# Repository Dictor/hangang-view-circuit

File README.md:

# hangang-view circuit
This is schemetic and gerber files repository of hangang-view project. Main code (MCU's firmware) is in [here](https://github.com/Dictor/hangang-view-code).

## schemetic image

## mcu pinout

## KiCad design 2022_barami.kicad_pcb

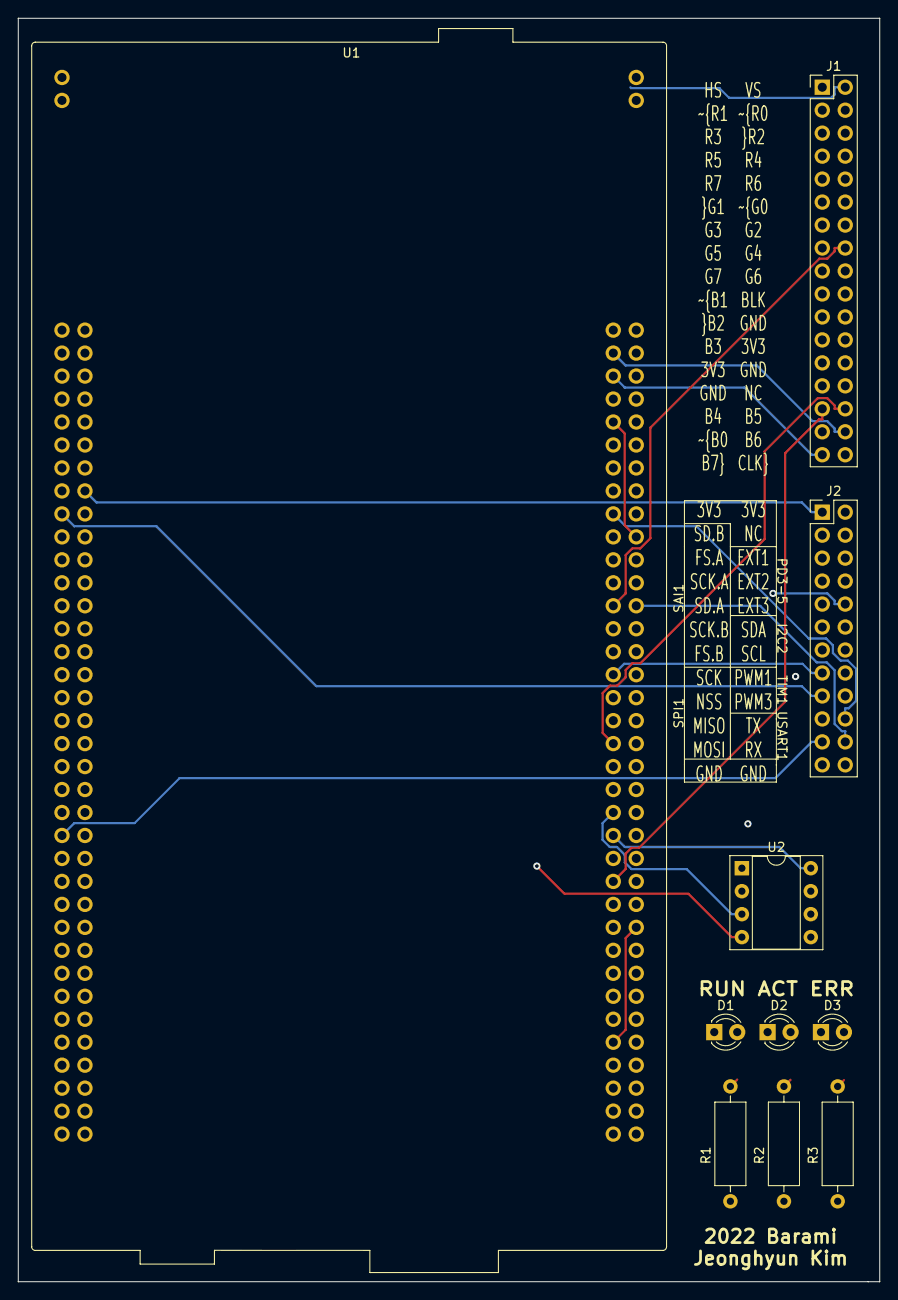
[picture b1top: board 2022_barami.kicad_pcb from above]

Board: 4 copper layers, 95.2 x 139.7 mm, 10 parts (0 on the bottom side), 53 nets.

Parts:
D1: LED_RUN; LED_D3.0mm
D2: LED_ACT; LED_D3.0mm
D3: LED_ERR; LED_D3.0mm
J1: GM7123 Module; PinHeader_2x17_P2.54mm_Vertical
J2: External IO; PinHeader_2x12_P2.54mm_Vertical
R1, R2, R3: 100R; R_Axial_DIN0309_L9.0mm_D3.2mm_P12.70mm_Horizontal
U1: NUCLEO144-H743ZI; ST_Morpho_Connector_144_STLink
U2: 23LC1024-E/P; DIP-8_W7.62mm_Socket

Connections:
+3V3: J1.24, J1.25, J2.1, J2.2, U1.16, U2.2
GND: D1.1, D2.1, D3.1, J1.3, J1.4, J1.6, J1.11, J1.12, J1.19, J1.21, J1.22, J1.26, J1.27, J1.31, J2.23, J2.24, U1.8, U1.19, U1.20, U1.22, U1.49, U1.60, U1.71, U1.72, U1.81, U1.92, U1.104, U1.111, U1.126, U1.135, U1.143, U1.144, U2.7
GPIO_EXT1: J2.6, U1.40
GPIO_EXT2: J2.8, U1.39
GPIO_EXT3: J2.10, U1.41
I2C2_SCL: J2.14, U1.51
I2C2_SDA: J2.12, U1.53
LCD_B3: J1.23, U1.95, U1.137
LCD_B4: J1.29, U1.121
LCD_B5: J1.30, U1.109
LCD_B6: J1.32, U1.75
LCD_B7: J1.33, U1.77
LCD_BLK: J1.20, U1.13
LCD_CLK: J1.34, U1.123
LCD_G2: J1.14, U1.85
LCD_G3: J1.13, U1.128
LCD_G4: J1.16, U1.97
LCD_G5: J1.15, U1.90
LCD_G6: J1.18, U1.91
LCD_G7: J1.17, U1.138
LCD_HSYNC: J1.1, U1.76
LCD_R3: J1.5, U1.34
LCD_R4: J1.8, U1.83
LCD_R5: J1.7, U1.38
LCD_R6: J1.10, U1.96
LCD_R7: J1.9, U1.125
LCD_VSYNC: J1.2, U1.32
LED_ACT: R3.1, U1.4
LED_ERR: R1.1, U1.57
LED_RUN: R2.1, U1.55
unnamed: D1.2, R1.2
unnamed: D2.2, R2.2
unnamed: D3.2, R3.2
QUADSPI_BK1_IO0: U1.117, U2.8
QUADSPI_BK1_IO1: U1.115, U2.3
QUADSPI_BK1_IO2: U1.46, U2.5
QUADSPI_BK1_IO3: U1.9, U2.4
QUADSPI_BK1_NCS: U1.142, U2.1
QUADSPI_CLK: U1.94, U2.6
SAI1_FS_A: J2.5, U1.48
SAI1_FS_B: J2.13, U1.56
SAI1_SCK_A: J2.7, U1.50
SAI1_SCK_B: J2.11, U1.54
SAI1_SD_A: J2.9, U1.62
SAI1_SD_B: J2.3, U1.47
SPI1_MISO: J2.19, U1.63
SPI1_MOSI: J2.21, U1.45
SPI1_NSS: J2.17, U1.17
SPI1_SCK: J2.15, U1.103
TIM1_CH1: J2.16, U1.124
TIM1_CH3: J2.18, U1.127
USART1_RX: J2.22, U1.98
USART1_TX: J2.20, U1.89

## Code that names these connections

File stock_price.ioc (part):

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Mcu.Name=STM32H743ZITx
Mcu.Package=LQFP144
Mcu.UserName=STM32H743ZITx
PA1.Mode=RMII
PA1.Signal=ETH_REF_CLK
PA10.Mode=OTG/Dual_Role_Device
PA10.Signal=USB_OTG_FS_ID
PA11.Mode=OTG/Dual_Role_Device
PA11.Signal=USB_OTG_FS_DM
PA12.Mode=OTG/Dual_Role_Device
PA12.Signal=USB_OTG_FS_DP
PA15\ (JTDI).Mode=NSS_Signal_Hard_Output
PA15\ (JTDI).Signal=SPI1_NSS
PA2.Mode=RMII
PA2.Signal=ETH_MDIO
PA3.Mode=RGB565
PA3.Signal=LTDC_B5
PA4.Mode=RGB565
PA4.Signal=LTDC_VSYNC
PA5.Mode=RGB565
PA5.Signal=LTDC_R4
PA6.Mode=RGB565
PA6.Signal=LTDC_G2
PA7.Mode=RMII
PA7.Signal=ETH_CRS_DV
PA9.Mode=Activate_VBUS
PA9.Signal=USB_OTG_FS_VBUS
PB0.Mode=RGB565
PB0.Signal=LTDC_R3
PB1.Mode=RGB565
PB1.Signal=LTDC_R6
PB10.Mode=RGB565
PB10.Signal=LTDC_G4
PB11.Mode=RGB565
PB11.Signal=LTDC_G5
PB12.Mode=RMII
PB12.Signal=ETH_TXD0
PB13.Mode=RMII
PB13.Signal=ETH_TXD1
PB14.GPIOParameters=GPIO_Label
PB14.GPIO_Label=LD3 [Red Led]
PB14.Signal=GPIO_Output
PB15.Mode=Asynchronous
PB15.Signal=USART1_RX
PB2.Mode=Single Bank 1
PB2.Signal=QUADSPI_CLK
PB3\ (JTDO/TRACESWO).Mode=Full_Duplex_Master
PB3\ (JTDO/TRACESWO).Signal=SPI1_SCK
PB6.Mode=Asynchronous
PB6.Signal=USART1_TX
PB8.Mode=RGB565
PB8.Signal=LTDC_B6
PB9.Mode=RGB565
PB9.Signal=LTDC_B7
PC0.Mode=RGB565
PC0.Signal=LTDC_R5
PC1.Mode=RMII
PC1.Signal=ETH_MDC
PC13.GPIOParameters=GPIO_Label
PC13.GPIO_Label=B1 [Blue PushButton]
PC13.Signal=GPIO_Input
PC14-OSC32_IN\ (OSC32_IN).Mode=LSE-External-Oscillator
PC14-OSC32_IN\ (OSC32_IN).Signal=RCC_OSC32_IN
PC15-OSC32_OUT\ (OSC32_OUT).Mode=LSE-External-Oscillator
PC15-OSC32_OUT\ (OSC32_OUT).Signal=RCC_OSC32_OUT
PC4.Mode=RMII
PC4.Signal=ETH_RXD0
PC5.Mode=RMII
PC5.Signal=ETH_RXD1
PC6.Mode=RGB565
PC6.Signal=LTDC_HSYNC
PC7.Mode=RGB565
PC7.Signal=LTDC_G6
PD0.GPIOParameters=GPIO_Label
PD0.GPIO_Label=LED_ERR
PD0.Signal=GPIO_Output
PD1.GPIOParameters=GPIO_Label
PD1.GPIO_Label=LED_RUN
PD1.Signal=GPIO_Output
PD10.Mode=RGB565
PD10.Signal=LTDC_B3
PD11.Mode=Single Bank 1
PD11.Signal=QUADSPI_BK1_IO0
PD12.Mode=Single Bank 1
PD12.Signal=QUADSPI_BK1_IO1
PD2.GPIOParameters=GPIO_Label
PD2.GPIO_Label=LED_ACT
PD2.Signal=GPIO_Output
PD3.GPIOParameters=GPIO_Label
PD3.GPIO_Label=GPIO_EXT1
PD3.Signal=GPIO_Output
PD4.GPIOParameters=GPIO_Label
PD4.GPIO_Label=GPIO_EXT2
PD4.Signal=GPIO_Output
PD5.GPIOParameters=GPIO_Label
PD5.GPIO_Label=GPIO_EXT3
PD5.Signal=GPIO_Output
PD7.Mode=Full_Duplex_Master
PD7.Signal=SPI1_MOSI
PD8.GPIOParameters=GPIO_Label
PD8.GPIO_Label=STLINK_RX
PD8.Mode=Asynchronous
PD8.Signal=USART3_TX
PD9.GPIOParameters=GPIO_Label
PD9.GPIO_Label=STLINK_TX
PD9.Mode=Asynchronous
PD9.Signal=USART3_RX
PE1.GPIOParameters=GPIO_Label
PE1.GPIO_Label=LD2 [Yellow Led]
PE1.Signal=GPIO_Output
PE11.Mode=RGB565
PE11.Signal=LTDC_G3
PE12.Mode=RGB565
PE12.Signal=LTDC_B4
PE13.Signal=S_TIM1_CH3
PE14.Mode=RGB565
PE14.Signal=LTDC_CLK
PE15.Mode=RGB565
PE15.Signal=LTDC_R7
PE2.Mode=Single Bank 1
PE2.Signal=QUADSPI_BK1_IO2
PE3.Mode=SAI_B_Master
PE3.Signal=SAI1_SD_B
PE4.Mode=SAI_A_Master
PE4.Signal=SAI1_FS_A
PE5.Mode=SAI_A_Master
PE5.Signal=SAI1_SCK_A
PE6.Mode=SAI_A_Master
PE6.Signal=SAI1_SD_A
PE9.Signal=S_TIM1_CH1
PF0.Mode=I2C
PF0.Signal=I2C2_SDA
PF1.Mode=I2C
PF1.Signal=I2C2_SCL
PF10.Mode=RGB565
PF10.Signal=LTDC_DE
PF6.Mode=Single Bank 1
PF6.Signal=QUADSPI_BK1_IO3
PF8.Mode=SAI_B_Master
PF8.Signal=SAI1_SCK_B
PF9.Mode=SAI_B_Master
PF9.Signal=SAI1_FS_B
PG11.Mode=RMII
PG11.Signal=ETH_TX_EN
PG6.Mode=Single Bank 1
PG6.Signal=QUADSPI_BK1_NCS
PG8.Mode=RGB565
PG8.Signal=LTDC_G7
PG9.Mode=Full_Duplex_Master
PG9.Signal=SPI1_MISO
PH0-OSC_IN\ (PH0).Mode=HSE-External-Clock-Source
PH0-OSC_IN\ (PH0).Signal=RCC_OSC_IN
PH1-OSC_OUT\ (PH1).Signal=RCC_OSC_OUT
RCC.HSE_VALUE=8000000
RCC.SYSCLKFreq_VALUE=480000000
RCC.SYSCLKSource=RCC_SYSCLKSOURCE_PLLCLK
board=NUCLEO-H743ZI2
boardIOC=true

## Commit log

2022-08-25 initial upload
2022-08-25 Add printed schematic
2022-09-25 Add some documentation and README
2022-09-25 Update schemetic with KiCAD files
2022-09-25 Correct mistypo
